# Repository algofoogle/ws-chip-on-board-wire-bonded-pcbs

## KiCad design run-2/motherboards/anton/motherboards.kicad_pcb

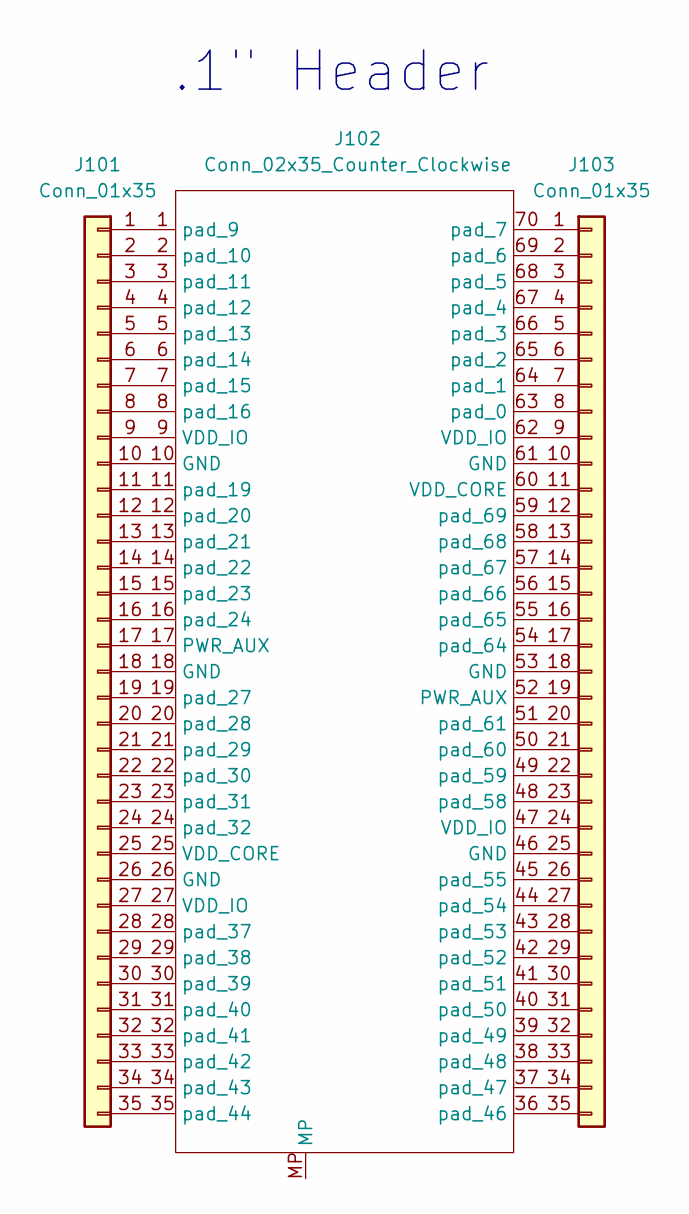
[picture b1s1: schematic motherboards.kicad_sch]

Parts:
J101, J103: Conn_01x35; PinHeader_1x35_P2.54mm_Vertical
J102: Conn_02x35_Counter_Clockwise; CONN-SMD_70P-P0.40_HCTL_HC-PBB40C-70DP-0.4V-02

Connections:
unnamed: J101.1, J102.1 (pad_9)
unnamed: J101.2, J102.2 (pad_10)
unnamed: J101.3, J102.3 (pad_11)
unnamed: J101.4, J102.4 (pad_12)
unnamed: J101.5, J102.5 (pad_13)
unnamed: J101.6, J102.6 (pad_14)
unnamed: J101.7, J102.7 (pad_15)
unnamed: J101.8, J102.8 (pad_16)
unnamed: J101.9, J102.9 (VDD_IO)
unnamed: J101.10, J102.10 (GND)
unnamed: J101.11, J102.11 (pad_19)
unnamed: J101.12, J102.12 (pad_20)
unnamed: J101.13, J102.13 (pad_21)
unnamed: J101.14, J102.14 (pad_22)
unnamed: J101.15, J102.15 (pad_23)
unnamed: J101.16, J102.16 (pad_24)
unnamed: J101.17, J102.17 (PWR_AUX)
unnamed: J101.18, J102.18 (GND)
unnamed: J101.19, J102.19 (pad_27)
unnamed: J101.20, J102.20 (pad_28)
unnamed: J101.21, J102.21 (pad_29)
unnamed: J101.22, J102.22 (pad_30)
unnamed: J101.23, J102.23 (pad_31)
unnamed: J101.24, J102.24 (pad_32)
unnamed: J101.25, J102.25 (VDD_CORE)
unnamed: J101.26, J102.26 (GND)
unnamed: J101.27, J102.27 (VDD_IO)
unnamed: J101.28, J102.28 (pad_37)
unnamed: J101.29, J102.29 (pad_38)
unnamed: J101.30, J102.30 (pad_39)
unnamed: J101.31, J102.31 (pad_40)
unnamed: J101.32, J102.32 (pad_41)
unnamed: J101.33, J102.33 (pad_42)
unnamed: J101.34, J102.34 (pad_43)
unnamed: J101.35, J102.35 (pad_44)
unnamed: J102.63 (pad_0), J103.8
unnamed: J102.64 (pad_1), J103.7
unnamed: J102.65 (pad_2), J103.6
unnamed: J102.66 (pad_3), J103.5
unnamed: J102.67 (pad_4), J103.4
unnamed: J102.68 (pad_5), J103.3
unnamed: J102.69 (pad_6), J103.2
unnamed: J102.70 (pad_7), J103.1
unnamed: J102.36 (pad_46), J103.35
unnamed: J102.37 (pad_47), J103.34
unnamed: J102.38 (pad_48), J103.33
unnamed: J102.39 (pad_49), J103.32
unnamed: J102.40 (pad_50), J103.31
unnamed: J102.41 (pad_51), J103.30
unnamed: J102.42 (pad_52), J103.29
unnamed: J102.43 (pad_53), J103.28
unnamed: J102.44 (pad_54), J103.27
unnamed: J102.45 (pad_55), J103.26
unnamed: J102.48 (pad_58), J103.23
unnamed: J102.49 (pad_59), J103.22
unnamed: J102.50 (pad_60), J103.21
unnamed: J102.51 (pad_61), J103.20
unnamed: J102.54 (pad_64), J103.17
unnamed: J102.55 (pad_65), J103.16
unnamed: J102.56 (pad_66), J103.15
unnamed: J102.57 (pad_67), J103.14
unnamed: J102.58 (pad_68), J103.13
unnamed: J102.59 (pad_69), J103.12
unnamed: J102.62 (VDD_IO), J103.9
unnamed: J102.61 (GND), J103.10
unnamed: J102.60 (VDD_CORE), J103.11
unnamed: J102.53 (GND), J103.18
unnamed: J102.52 (PWR_AUX), J103.19
unnamed: J102.47 (VDD_IO), J103.24
unnamed: J102.46 (GND), J103.25

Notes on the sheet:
.1" Header

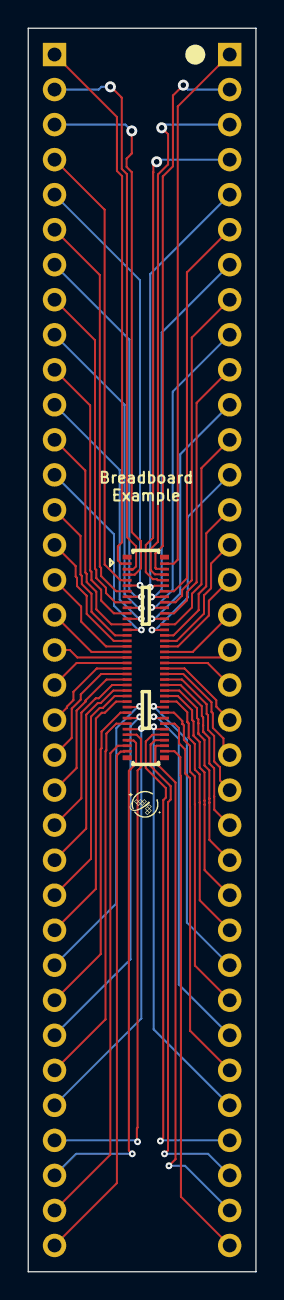
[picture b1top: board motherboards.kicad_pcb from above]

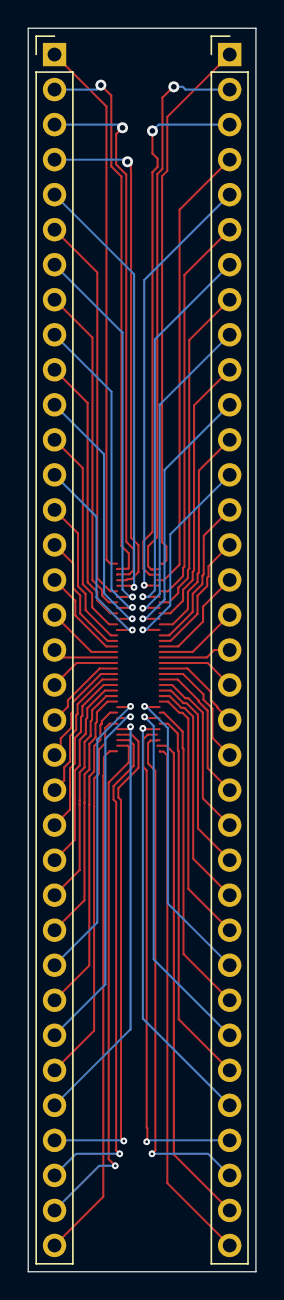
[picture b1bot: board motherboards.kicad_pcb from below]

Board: 2 copper layers, 16.5 x 90.2 mm, 3 parts (2 on the bottom side), 70 nets.
